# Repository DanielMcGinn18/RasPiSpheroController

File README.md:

# Sphero Remote Control for Raspberry Pi
## Designed by researchers at the Tufts CEEO in Summer 2018

Python Files:
* BB8_driver.py - <a href="https://github.com/jjinking/SpheroBB8-python/blob/master/BB8_driver.py">Library used to implement high-level controls</a>
* sphero_keycommands.py - Control Sphero with keyboard
* sphero_remote.py - Control Sphero with Custom Raspberry Pi hat

Board Files:
* EAGLE schematic and board files for simple controller (sphero_remote.py is written for this board)
* EAGLE schematic for board version 2 with added functionality:
* Can be stacked on top of the <a href="https://www.adafruit.com/product/3196">Pimoroni LiPo SHIM</a>
* Single RGB LED
* Potentiometer and 10-bit ADC to allow user to change Sphero speed
* Through hole connection to Raspberry Pi

CAD Files:
* Raspberry Pi case for simple controller

To install bluepy run:
```
sudo apt-get install python-pip libglib2.0-dev
sudo pip install bluepy
```

Add the MAC address of your sphero to line 10 of BB8_driver.py

To run the program on your raspberry pi at startup enter the command: sudo nano /home/pi/.bashrc
go to the last line of the script and add:
echo Running at boot
sudo python <complete sphero_remote.py file path>

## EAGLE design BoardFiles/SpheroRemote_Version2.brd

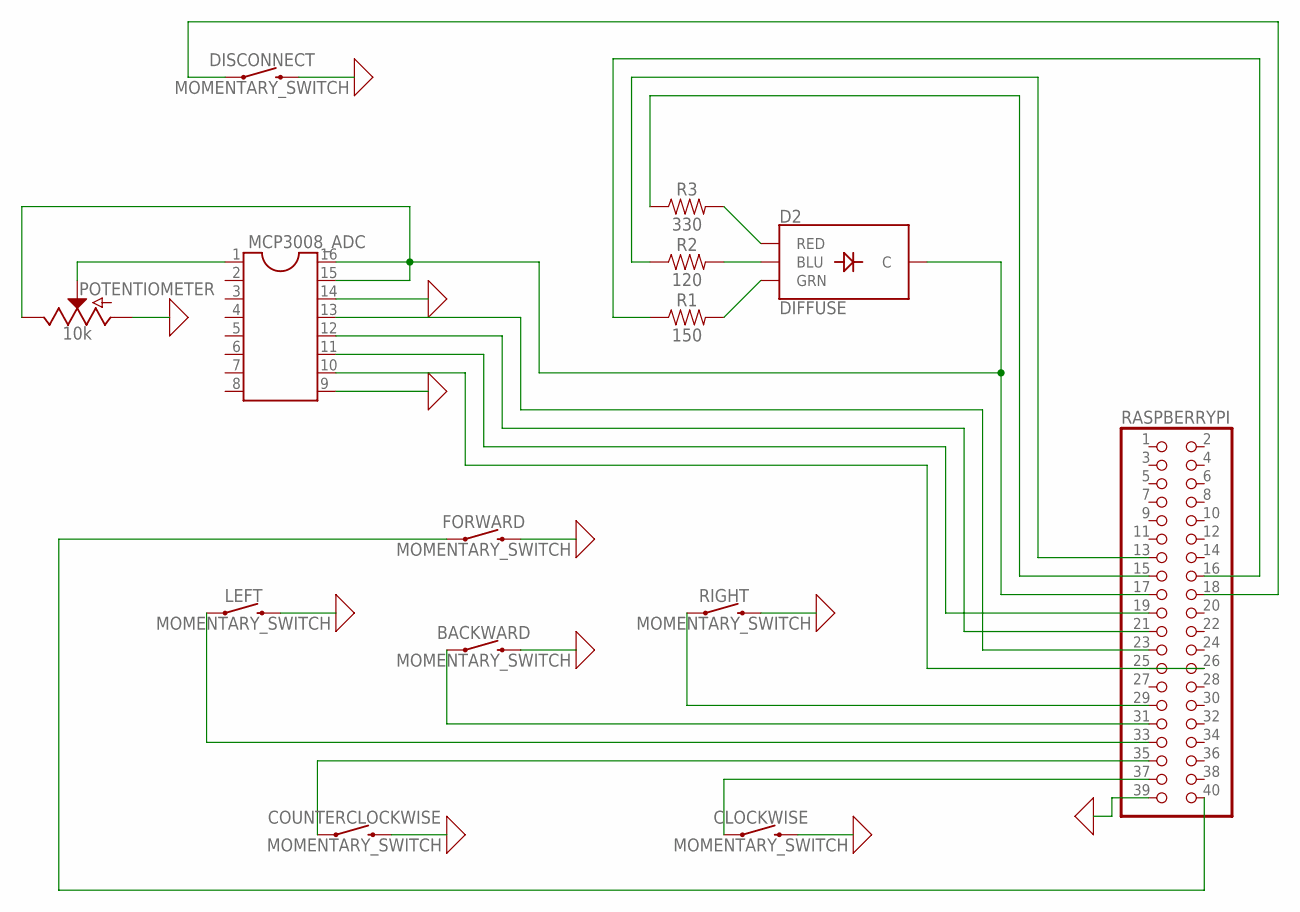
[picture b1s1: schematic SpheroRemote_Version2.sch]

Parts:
BACKWARD: MOMENTARY_SWITCH; TACTILE_SWITCH_PTH_12MM
CLOCKWISE: MOMENTARY_SWITCH; TACTILE_SWITCH_PTH_12MM
COUNTERCLOCKWISE: MOMENTARY_SWITCH; TACTILE_SWITCH_PTH_12MM
D2: DIFFUSE; LED-RGB-THRU
DISCONNECT: MOMENTARY_SWITCH; TACTILE_SWITCH_PTH_12MM
FORWARD: MOMENTARY_SWITCH; TACTILE_SWITCH_PTH_12MM
LEFT: MOMENTARY_SWITCH; TACTILE_SWITCH_PTH_12MM
MCP3008_ADC: DIL16
POTENTIOMETER: 10k; POT-PTH-ALPS-KIT
R1: 150; AXIAL-0.3
R2: 120; AXIAL-0.3
R3: 330; AXIAL-0.3
RASPBERRYPI: PINHD-2X20; 2X20
RIGHT: MOMENTARY_SWITCH; TACTILE_SWITCH_PTH_12MM

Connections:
0: BACKWARD.3 (2), CLOCKWISE.3 (2), COUNTERCLOCKWISE.3 (2), DISCONNECT.3 (2), FORWARD.3 (2), LEFT.3 (2), MCP3008_ADC.9, MCP3008_ADC.14, POTENTIOMETER.P$3 (A), RASPBERRYPI.39, RIGHT.3 (2)
unnamed: D2.3 (GRN), R1.P$2 (2)
unnamed: R3.P$1 (1), RASPBERRYPI.15
unnamed: D2.4 (BLU), R2.P$2 (2)
unnamed: MCP3008_ADC.1, POTENTIOMETER.P$2 (S)
unnamed: LEFT.1, RASPBERRYPI.33
unnamed: BACKWARD.1, RASPBERRYPI.31
unnamed: RASPBERRYPI.29, RIGHT.1
unnamed: CLOCKWISE.1, RASPBERRYPI.37
unnamed: COUNTERCLOCKWISE.1, RASPBERRYPI.35
unnamed: D2.1 (RED), R3.P$2 (2)
unnamed: MCP3008_ADC.13, RASPBERRYPI.23
unnamed: R2.P$1 (1), RASPBERRYPI.13
unnamed: MCP3008_ADC.12, RASPBERRYPI.21
unnamed: MCP3008_ADC.11, RASPBERRYPI.19
unnamed: D2.2 (C), MCP3008_ADC.15, MCP3008_ADC.16, POTENTIOMETER.P$1 (E), RASPBERRYPI.17
unnamed: MCP3008_ADC.10, RASPBERRYPI.26
unnamed: DISCONNECT.1, RASPBERRYPI.18
unnamed: FORWARD.1, RASPBERRYPI.40
unnamed: R1.P$1 (1), RASPBERRYPI.16

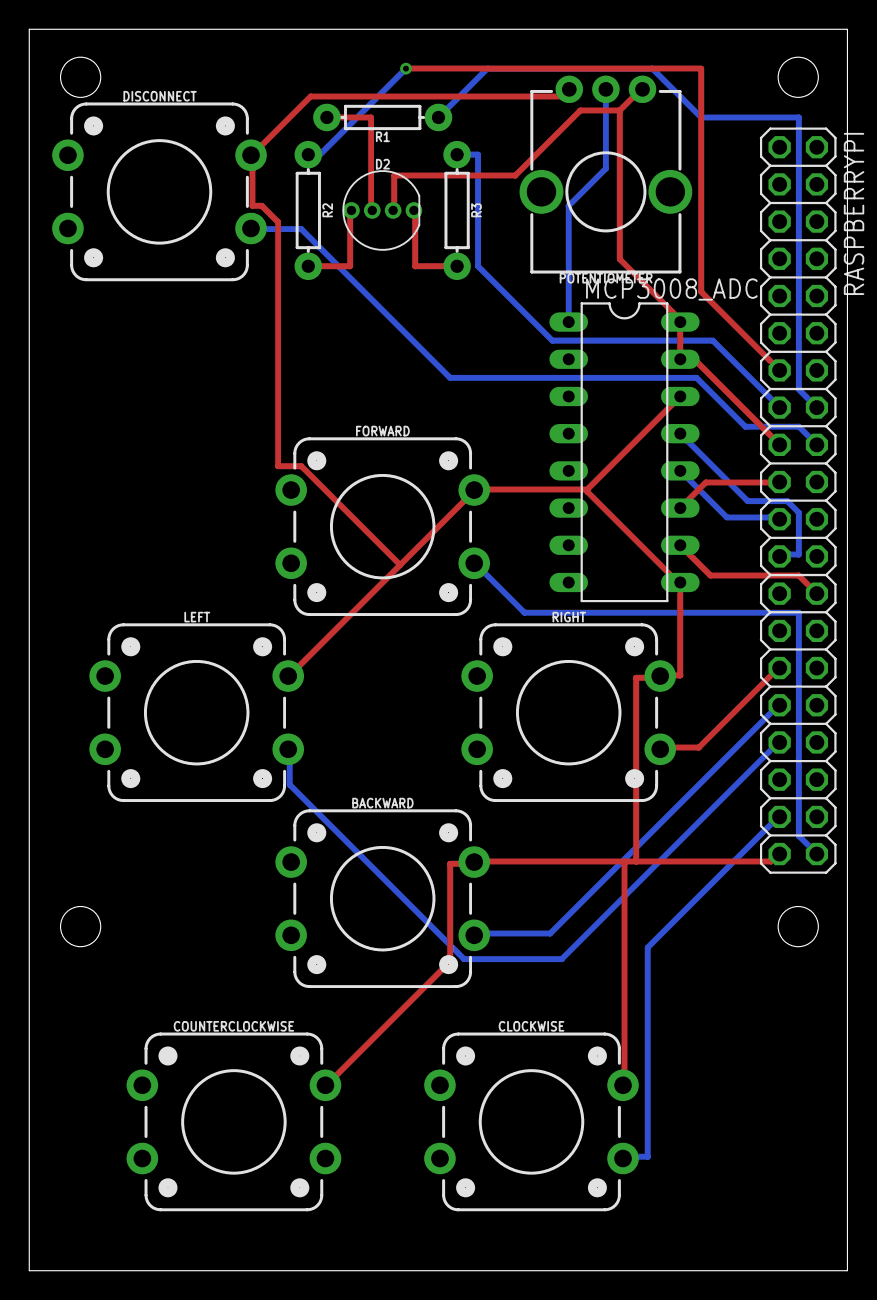
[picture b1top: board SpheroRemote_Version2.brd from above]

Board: 2 copper layers, 55.9 x 84.8 mm, 14 parts (0 on the bottom side), 20 nets.

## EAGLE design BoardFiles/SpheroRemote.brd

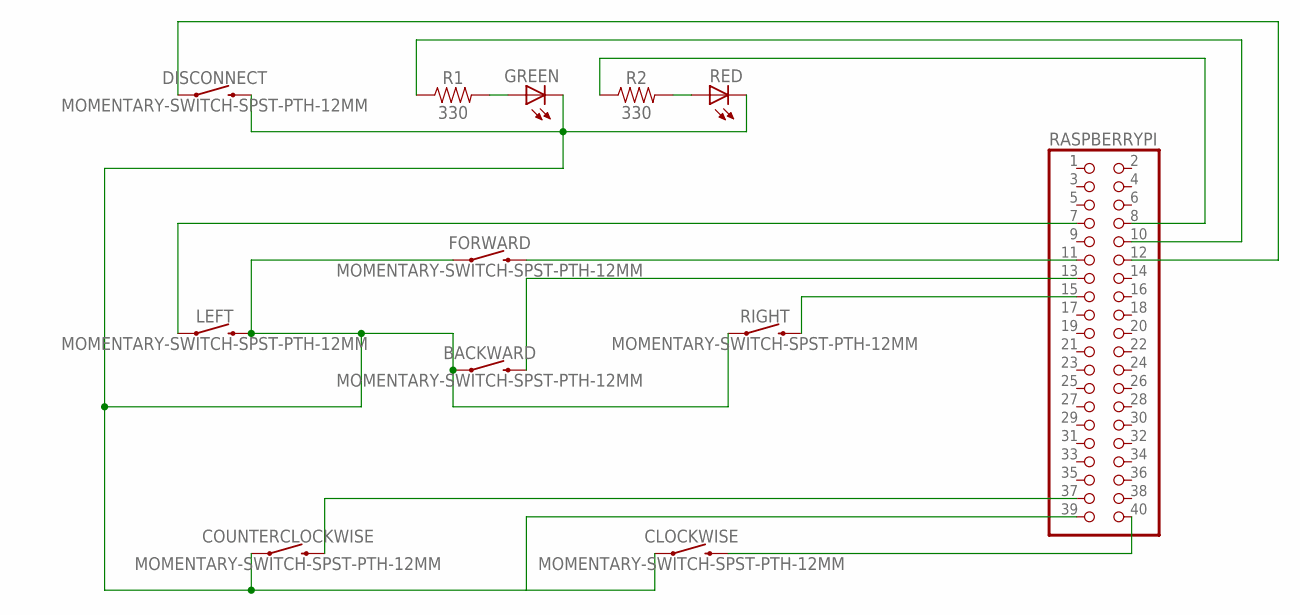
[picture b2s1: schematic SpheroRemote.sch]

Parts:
BACKWARD: MOMENTARY-SWITCH-SPST-PTH-12MM; TACTILE_SWITCH_PTH_12MM
CLOCKWISE: MOMENTARY-SWITCH-SPST-PTH-12MM; TACTILE_SWITCH_PTH_12MM
COUNTERCLOCKWISE: MOMENTARY-SWITCH-SPST-PTH-12MM; TACTILE_SWITCH_PTH_12MM
DISCONNECT: MOMENTARY-SWITCH-SPST-PTH-12MM; TACTILE_SWITCH_PTH_12MM
FORWARD: MOMENTARY-SWITCH-SPST-PTH-12MM; TACTILE_SWITCH_PTH_12MM
GREEN: LED5MM
LEFT: MOMENTARY-SWITCH-SPST-PTH-12MM; TACTILE_SWITCH_PTH_12MM
R1, R2: 330; AXIAL-0.3
RASPBERRYPI: PINHD-2X20; 2X20
RED: LED5MM
RIGHT: MOMENTARY-SWITCH-SPST-PTH-12MM; TACTILE_SWITCH_PTH_12MM

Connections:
unnamed: R2.P$2 (2), RED.A
unnamed: CLOCKWISE.3 (2), RASPBERRYPI.40
unnamed: COUNTERCLOCKWISE.3 (2), RASPBERRYPI.37
unnamed: R2.P$1 (1), RASPBERRYPI.8
unnamed: R1.P$1 (1), RASPBERRYPI.10
unnamed: GREEN.A, R1.P$2 (2)
unnamed: BACKWARD.1, CLOCKWISE.1, COUNTERCLOCKWISE.1, DISCONNECT.3 (2), FORWARD.1, GREEN.K (C), LEFT.3 (2), RASPBERRYPI.39, RED.K (C), RIGHT.1
unnamed: LEFT.1, RASPBERRYPI.7
unnamed: FORWARD.3 (2), RASPBERRYPI.11
unnamed: BACKWARD.3 (2), RASPBERRYPI.13
unnamed: RASPBERRYPI.15, RIGHT.3 (2)
unnamed: DISCONNECT.1, RASPBERRYPI.12

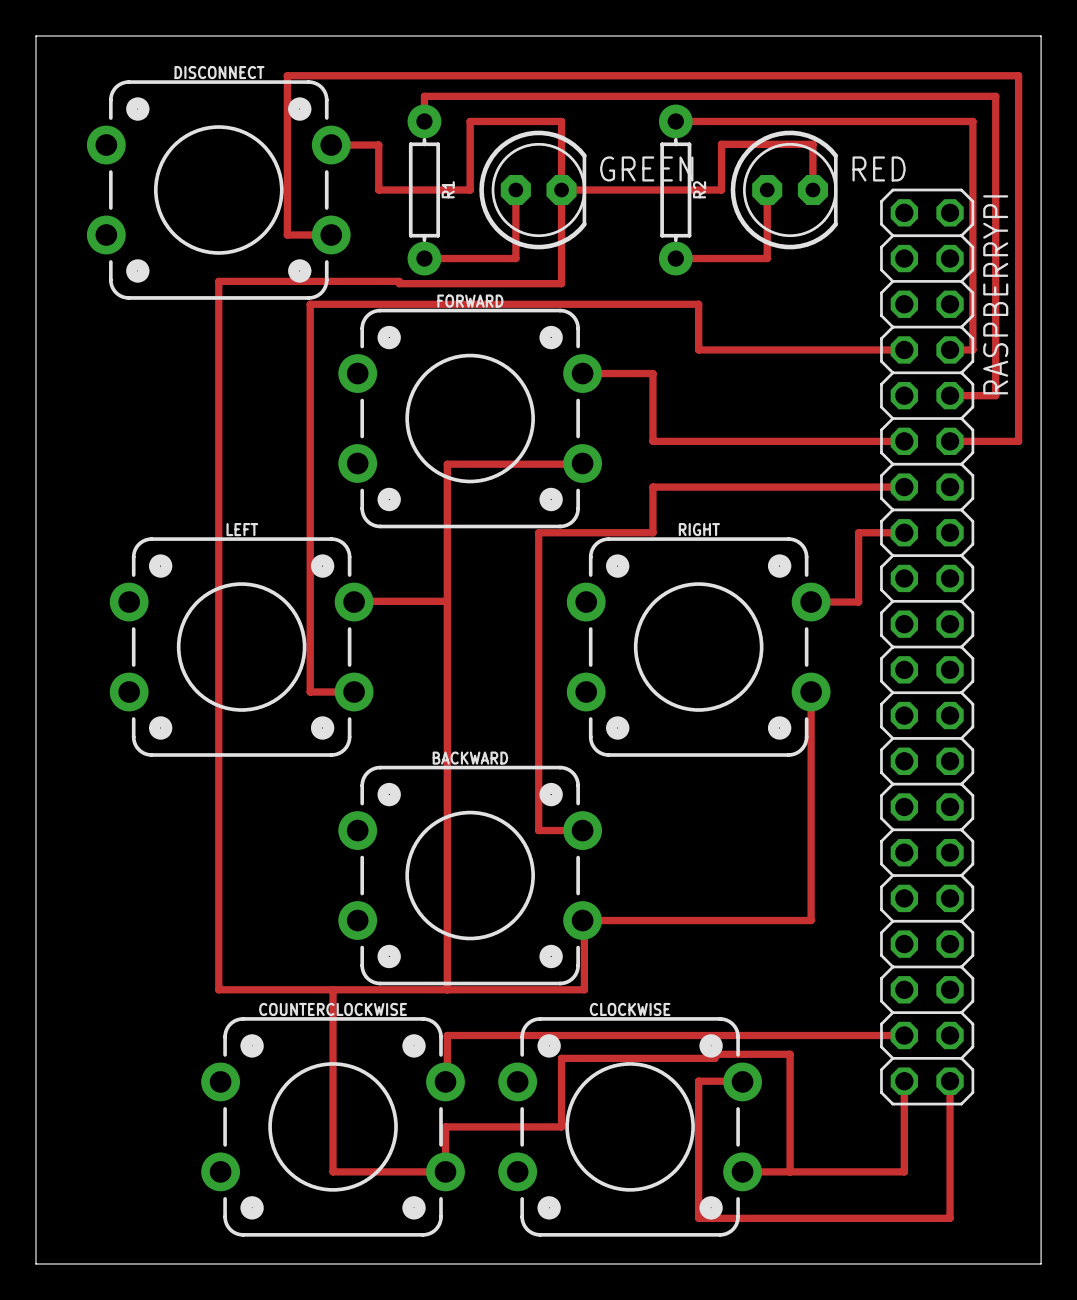
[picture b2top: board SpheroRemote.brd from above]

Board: 2 copper layers, 55.9 x 68.2 mm, 12 parts (0 on the bottom side), 12 nets.

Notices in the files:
parts and their libraries:
SparkFun-Switches: Licensing: Creative Commons ShareAlike 4.0 International - https://creativecommons.org/licenses/by-sa/4.0
